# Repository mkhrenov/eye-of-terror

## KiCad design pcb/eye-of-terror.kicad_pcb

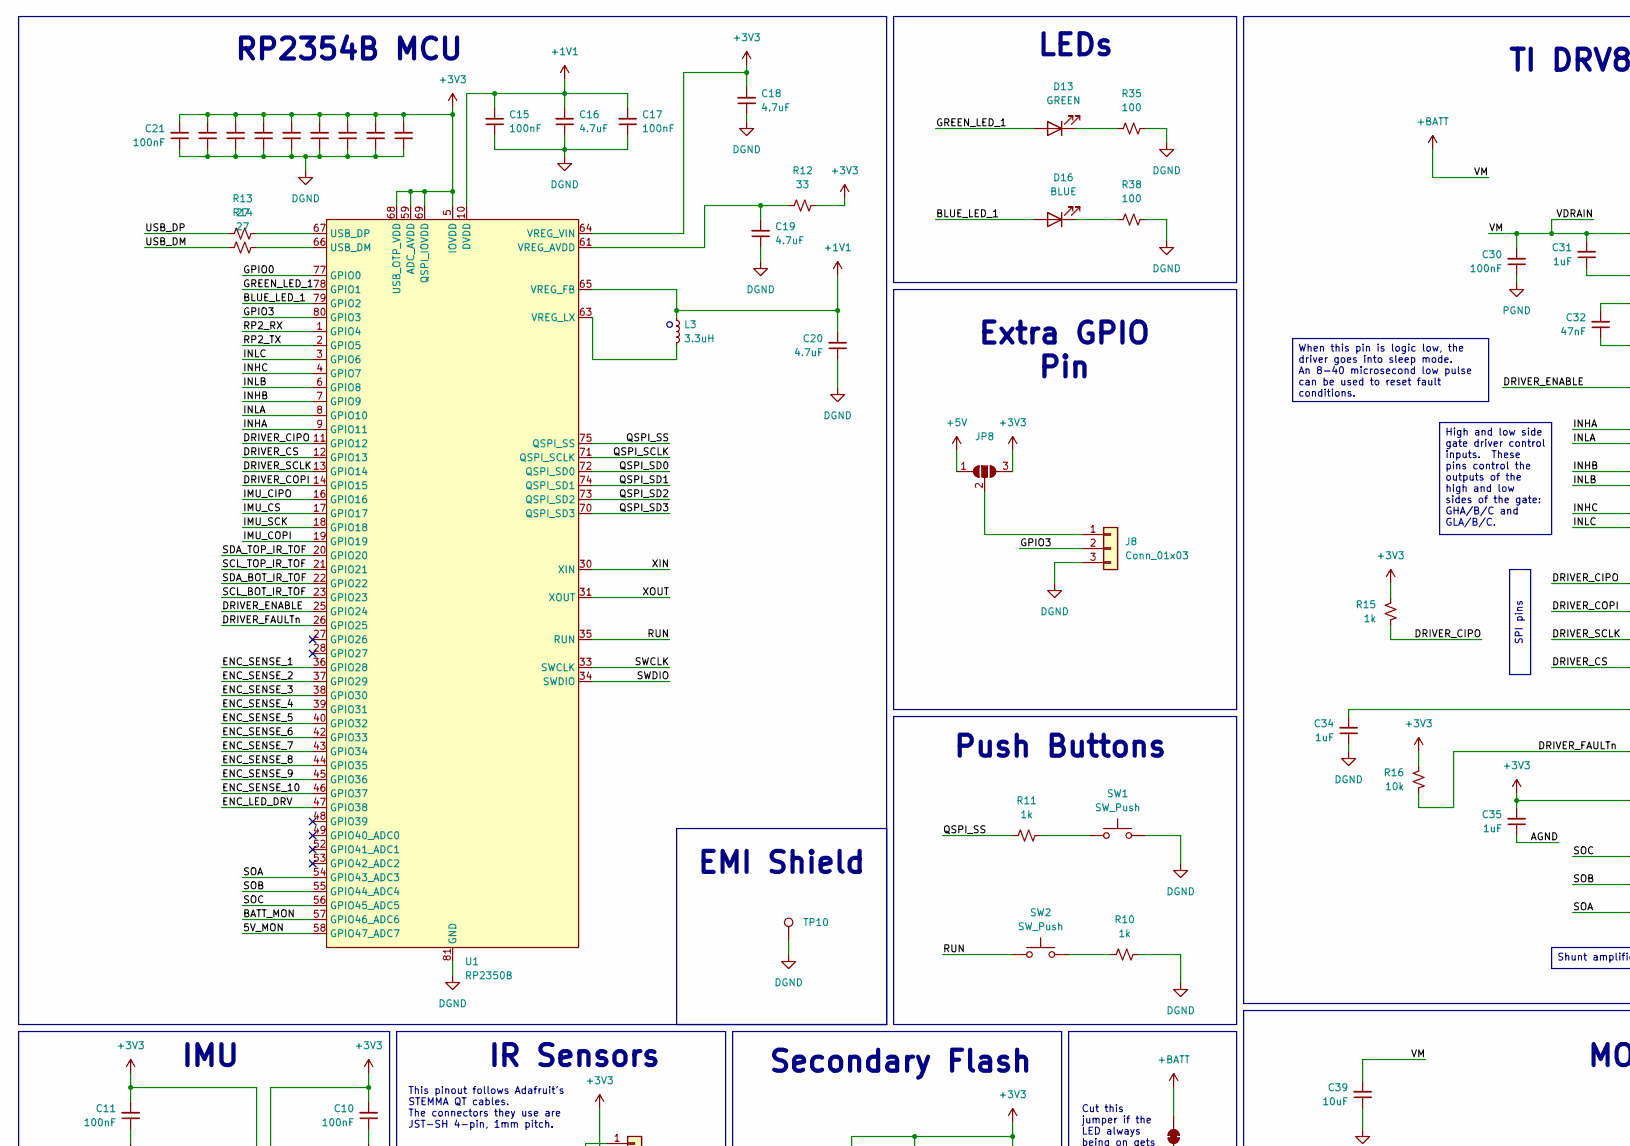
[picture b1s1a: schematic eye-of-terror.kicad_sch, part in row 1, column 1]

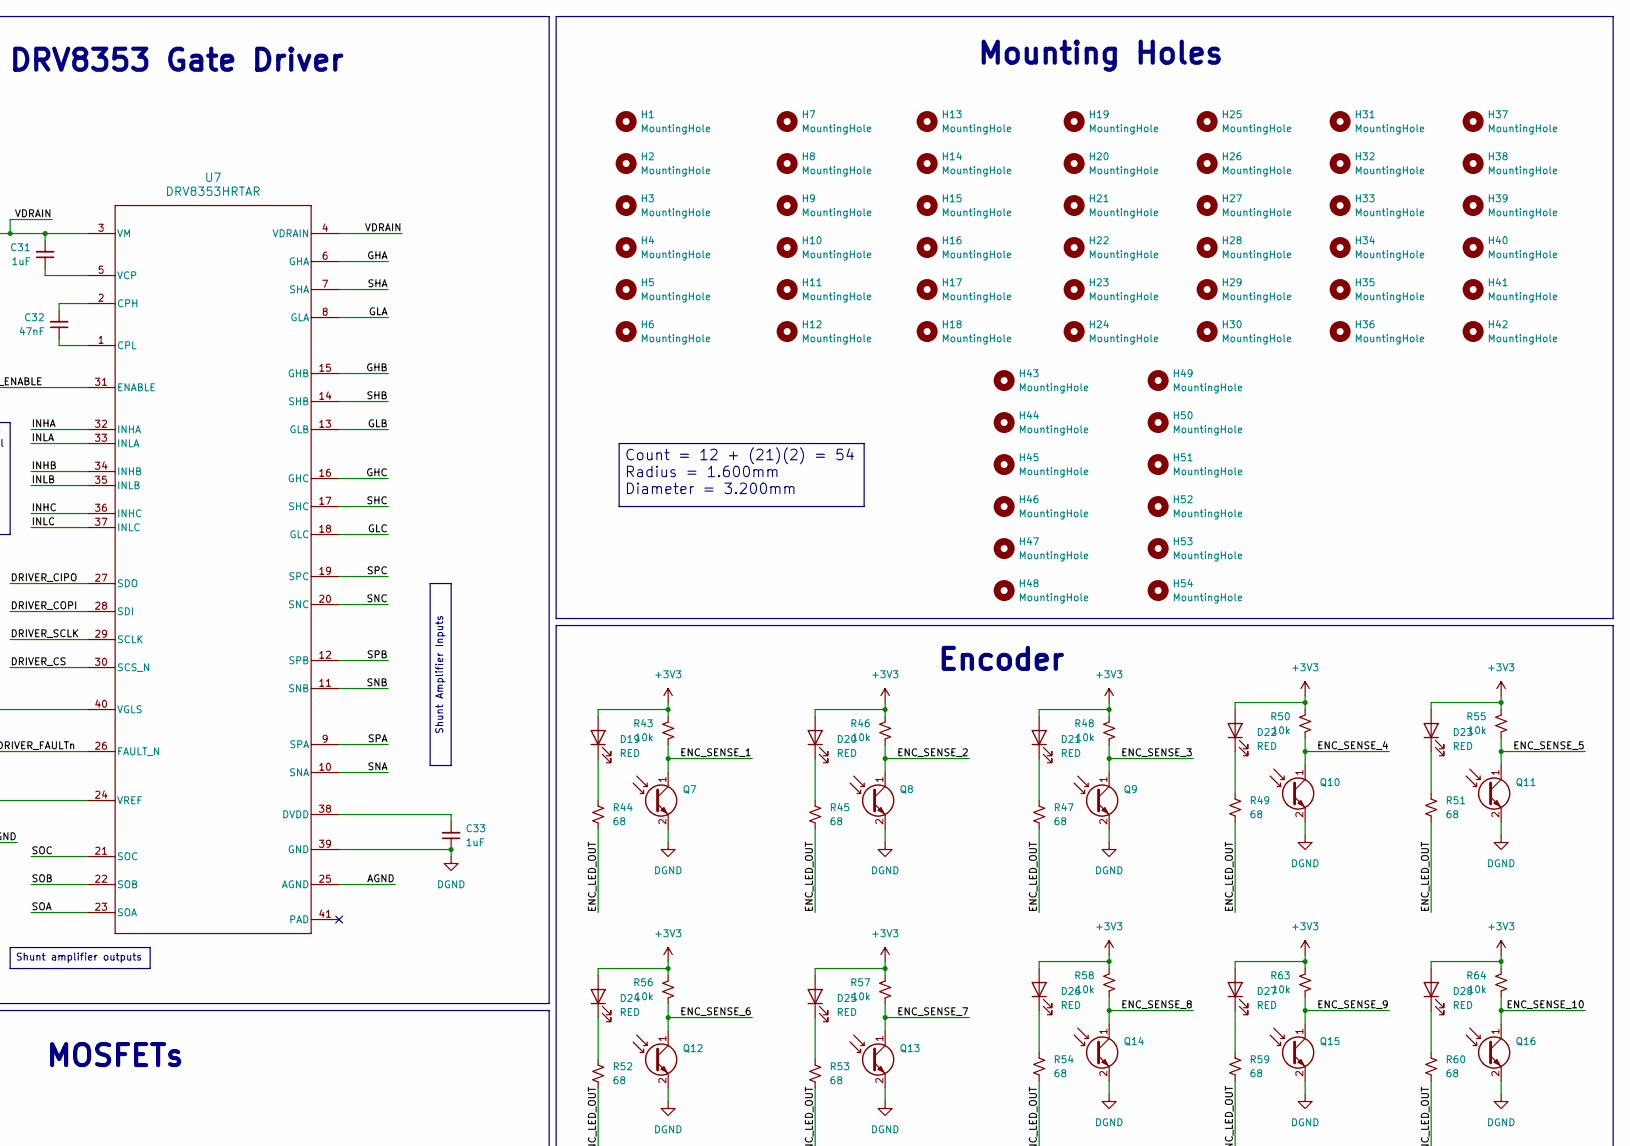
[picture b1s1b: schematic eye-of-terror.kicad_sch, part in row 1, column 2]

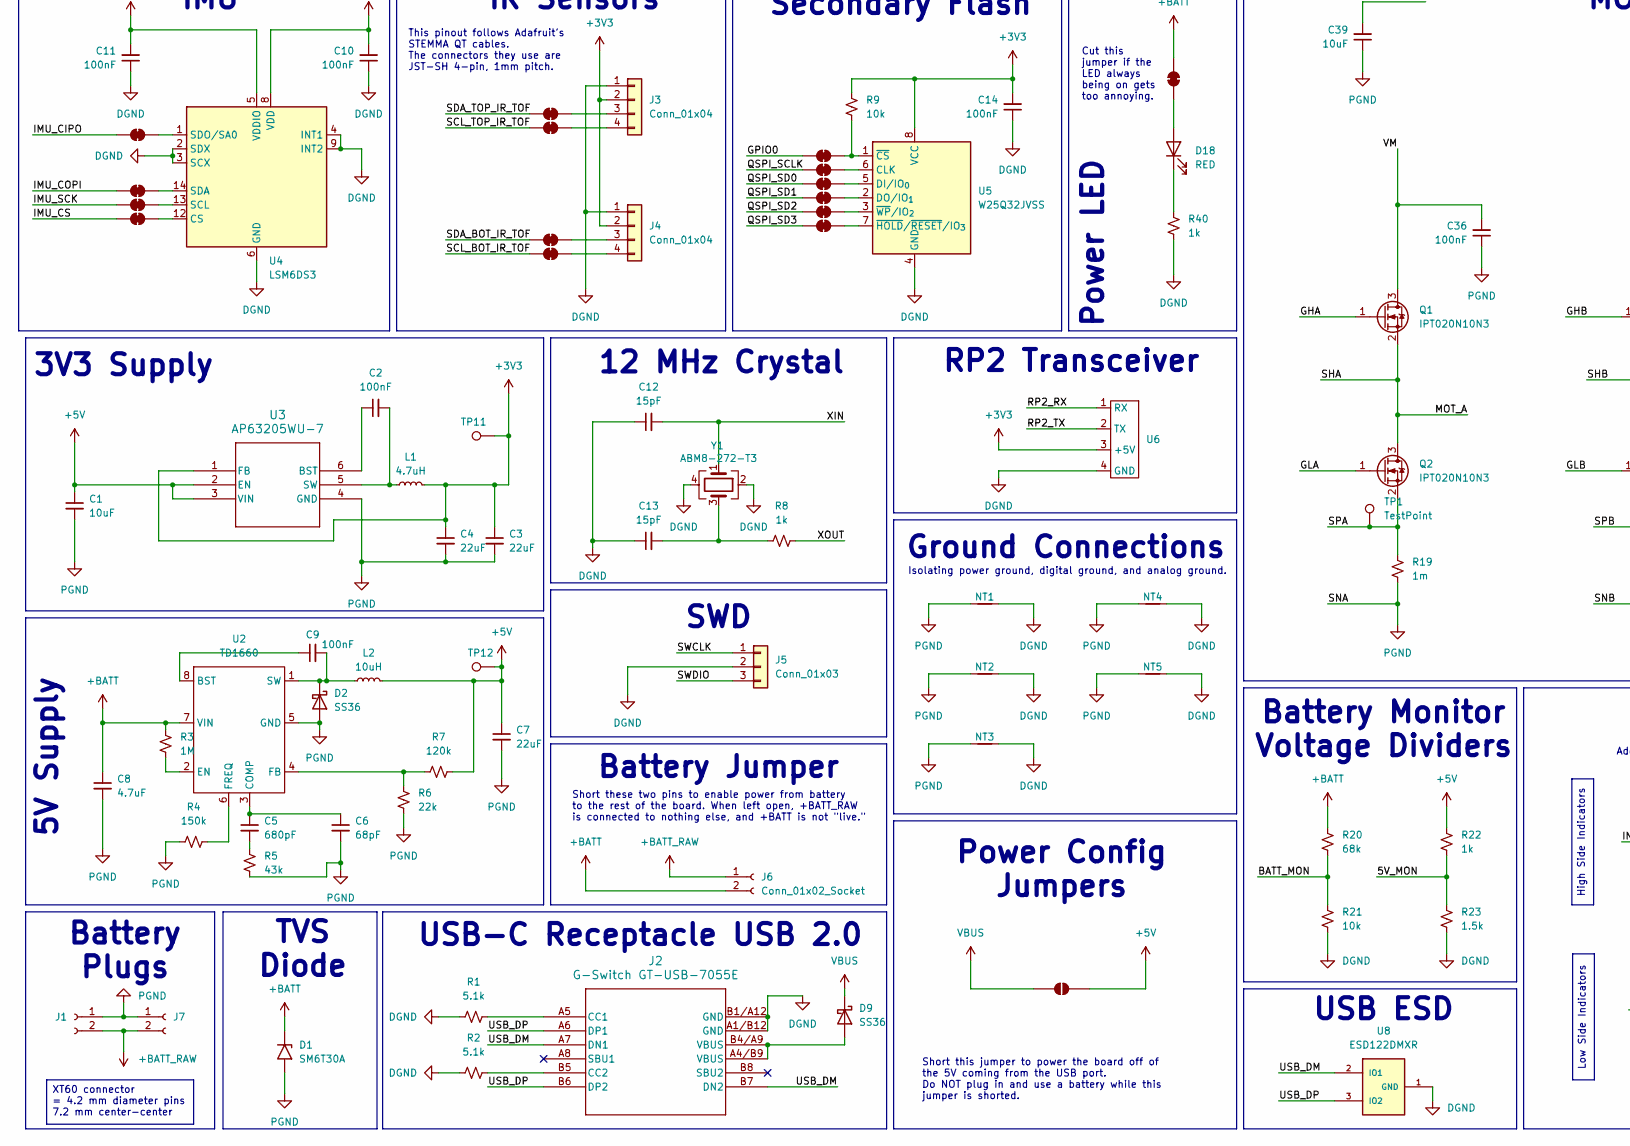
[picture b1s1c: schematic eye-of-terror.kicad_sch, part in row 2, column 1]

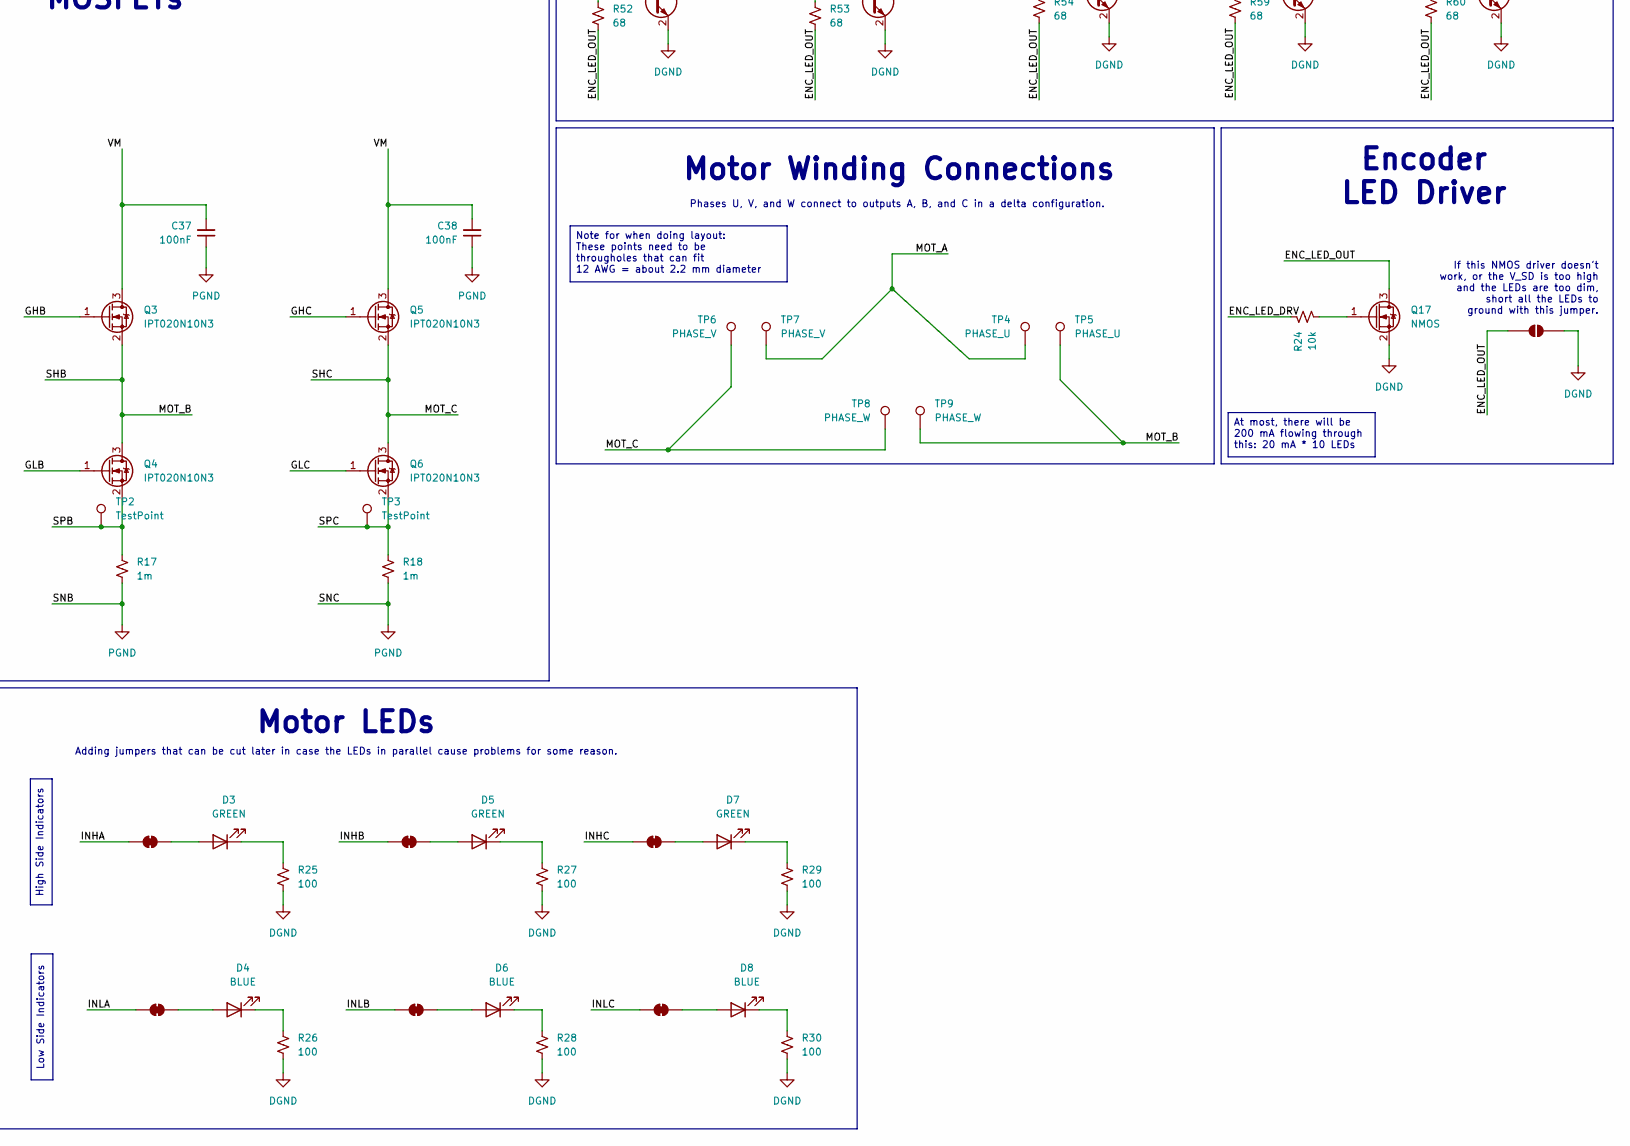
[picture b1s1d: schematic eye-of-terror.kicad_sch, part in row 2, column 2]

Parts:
C1, C39: 10uF; CP_Elec_5x5.4; LCSC Number C72487
C2, C9, C30, C36, C37, C38: 100nF; C_0603_1608Metric_Pad1.08x0.95mm_HandSolder; LCSC Number C14663
C3, C4, C7: 22uF; C_0603_1608Metric_Pad1.08x0.95mm_HandSolder; LCSC Number C86295
C5: 680pF; C_0402_1005Metric_Pad0.74x0.62mm_HandSolder; LCSC Number C307451
C6: 68pF; C_0603_1608Metric_Pad1.08x0.95mm_HandSolder; LCSC Number C62782
C8, C16, C18, C19, C20: 4.7uF; C_0402_1005Metric_Pad0.74x0.62mm_HandSolder; LCSC Number C23733
C10, C11, C14, C15, C17, C21, C22, C23, C24, C25, C26, C27, C28, C29: 100nF; C_0402_1005Metric_Pad0.74x0.62mm_HandSolder; LCSC Number C60474
C12, C13: 15pF; C_0402_1005Metric_Pad0.74x0.62mm_HandSolder; LCSC Number C86285
C31, C33, C34, C35: 1uF; C_0603_1608Metric_Pad1.08x0.95mm_HandSolder; LCSC Number C15849
C32: 47nF; C_0402_1005Metric_Pad0.74x0.62mm_HandSolder; LCSC Number C368599
D1: SM6T30A; D_SMB; LCSC Number C110904
D2, D9: SS36; D_SMB; LCSC Number C35490
D3, D5, D7, D13: GREEN; D_1206_3216Metric_Pad1.42x1.75mm_HandSolder; LCSC Number C965825
D4, D6, D8, D16: BLUE; D_1206_3216Metric_Pad1.42x1.75mm_HandSolder; LCSC Number C965827
D18, D19, D20, D21, D22, D23, D24, D25, D26, D27, D28: RED; D_1206_3216Metric_Pad1.42x1.75mm_HandSolder; LCSC Number C2984265
H1, H2, H3, H4, H5, H6, H7, H8, H9, H10, H11, H12, H13, H14, H15, H16, H17, H18, H19, H20, H21, H22, H23, H24, H25, H26, H27, H28, H29, H30, H31, H32, H33, H34, H35, H36, H37, H38, H39, H40, H41, H42, H43, H44, H45, H46, H47, H48, H49, H50, H51, H52, H53, H54: MountingHole; MountingHole_3.2mm_M3
J1, J6, J7: Conn_01x02_Socket; AMASS_XT60-M_1x02_P7.20mm_Vertical
J2: G-Switch GT-USB-7055E; CONN_GT-USB-7055A_GSW; LCSC Number C7450622
J3, J4: Conn_01x04; PinHeader_1x04_P1.00mm_Vertical
J5, J8: Conn_01x03; PinHeader_1x03_P2.54mm_Vertical
JP1, JP2, JP3, JP4, JP5, JP6, JP7, JP9, JP10, JP11, JP12, JP13, JP14, JP15, JP16, JP19, JP20, JP21, JP22, JP23, JP24: SolderJumper_2_Bridged; SolderJumper-2_P1.3mm_Bridged_RoundedPad1.0x1.5mm
JP8: SolderJumper_3_Open; SolderJumper-3_P1.3mm_Open_RoundedPad1.0x1.5mm_NumberLabels
JP17, JP18: SolderJumper_2_Bridged; SolderJumper-2_P1.3mm_Open_RoundedPad1.0x1.5mm
L1: 4.7uH; IND_LQH5BPZ4R7NT0L; LCSC Number C703747
L2: 10uH; L_Sunlord_MWSA0402S; LCSC Number C2921170
L3: 3.3uH; ABRACON-AOTA-B201610S3R3-101-T; LCSC Number C42411119
NT1, NT2, NT3, NT4, NT5: NetTie_2; NetTie-2_SMD_Pad2.0mm
Q1, Q2, Q3, Q4, Q5, Q6: IPT020N10N3; Infineon_PG-HSOF-8-1_ThermalVias; LCSC Number C537070
Q7, Q8, Q9, Q10, Q11, Q12, Q13, Q14, Q15, Q16: ALS-PT19-315C/L177/TR8; LED_0603_1608Metric_Pad1.05x0.95mm_HandSolder; LCSC Number C146233
Q17: NMOS; TSOT-23_HandSoldering
R1, R2: 5.1k; R_0402_1005Metric_Pad0.72x0.64mm_HandSolder; LCSC Number C114759
R3: 1M; R_0603_1608Metric_Pad0.98x0.95mm_HandSolder; LCSC Number C105578
R4: 150k; R_0402_1005Metric_Pad0.72x0.64mm_HandSolder; LCSC Number C93947
R5: 43k; R_0603_1608Metric_Pad0.98x0.95mm_HandSolder; LCSC Number C2907038
R6: 22k; R_0603_1608Metric_Pad0.98x0.95mm_HandSolder; LCSC Number C114065
R7: 120k; R_0603_1608Metric_Pad0.98x0.95mm_HandSolder; LCSC Number C114607
R8, R10, R11, R15, R22: 1k; R_0402_1005Metric_Pad0.72x0.64mm_HandSolder; LCSC Number C106235
R9, R16, R21, R24, R43, R46, R48, R50, R55, R56, R57, R58, R63, R64: 10k; R_0402_1005Metric_Pad0.72x0.64mm_HandSolder; LCSC Number C60490
R12: 33; R_0402_1005Metric_Pad0.72x0.64mm_HandSolder; LCSC Number C138002
R13, R14: 27; R_0402_1005Metric_Pad0.72x0.64mm_HandSolder; LCSC Number C25100
R17, R18, R19: 1m; R_1206_3216Metric_Pad1.30x1.75mm_HandSolder; LCSC Number C7467246
R20: 68k; R_0603_1608Metric_Pad0.98x0.95mm_HandSolder; LCSC Number C23231
R23: 1.5k; R_1210_3225Metric_Pad1.30x2.65mm_HandSolder; LCSC Number C3000602
R25, R26, R27, R28, R29, R30, R35, R38: 100; R_0603_1608Metric_Pad0.98x0.95mm_HandSolder; LCSC Number C105588
R40: 1k; R_0603_1608Metric_Pad0.98x0.95mm_HandSolder; LCSC Number C22548
R44, R45, R47, R49, R51, R52, R53, R54, R59, R60: 68; R_0402_1005Metric_Pad0.72x0.64mm_HandSolder; LCSC Number C163455
SW1, SW2: SW_Push; SW_Push_SPST_NO_Alps_SKRK; LCSC Number C720477
TP1, TP2, TP3: TestPoint; TestPoint_Pad_D2.5mm
TP4, TP5: PHASE_U; THTPad_D5.0mm_Drill2.5mm
TP6, TP7: PHASE_V; THTPad_D5.0mm_Drill2.5mm
TP8, TP9: PHASE_W; THTPad_D5.0mm_Drill2.5mm
TP10: TestPoint; shielding
TP11, TP12: TestPoint; TestPoint_Pad_D1.0mm
U1: RP2350B; QFN-80-1EP_10x10mm_P0.4mm_EP3.4x3.4mm_ThermalVias; LCSC Number C39843328
U2: TD1660; TD1660-SOIC-8; LCSC Number C2832211
U3: AP63205WU-7; SOIC_05WU-7_DIO; LCSC Number C780769
U4: LSM6DS3; LGA-14_3x2.5mm_P0.5mm_LayoutBorder3x4y; LCSC Number C95230
U5: W25Q32JVSS; SOIC-8_5.3x5.3mm_P1.27mm; LCSC Number C97521
U6: RP2
U7: DRV8353HRTAR; RTA0040B; LCSC Number C1518717
U8: ESD122DMXR; IC_ESD122DMXR; PARTREV A
Y1: ABM8-272-T3; Crystal_SMD_3225-4Pin_3.2x2.5mm; LCSC Number C20625731

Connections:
+1V1: C15.2, C16.2, C17.2, C20.2, L3.1, U1.10 (DVDD), U1.32 (DVDD), U1.51 (DVDD), U1.65 (VREG_FB)
+3V3: C3.1, C4.1, C10.2, C11.2, C14.2, C18.2, C21.2, C22.2, C23.2, C24.2, C25.2, C26.2, C27.2, C28.2, C29.2, C35.2, D19.2 (A), D20.2 (A), D21.2 (A), D22.2 (A), D23.2 (A), D24.2 (A), D25.2 (A), D26.2 (A), D27.2 (A), D28.2 (A), J3.2, J4.2, JP8.3 (B), L1.2, R9.1, R12.2, R15.1, R16.1, R43.1, R46.1, R48.1, R50.1, R55.1, R56.1, R57.1, R58.1, R63.1, R64.1, TP11.1 (1_1), U1.5 (IOVDD), U1.15 (IOVDD), U1.24 (IOVDD), U1.29 (IOVDD), U1.41 (IOVDD), U1.50 (IOVDD), U1.59 (ADC_AVDD), U1.60 (IOVDD), U1.64 (VREG_VIN), U1.68 (USB_OTP_VDD), U1.69 (QSPI_IOVDD), U1.76 (IOVDD), U3.1 (FB), U4.5 (VDDIO), U4.8 (VDD), U5.8 (VCC), U6.3 (+5V), U7.24 (VREF)
+5V: C1.1, C7.1, JP8.1 (A), JP17.2 (B), L2.2, R7.2, R22.1, TP12.1 (1_1), U3.2 (EN), U3.3 (VIN)
+BATT: C8.1, C30.2, C31.2, C36.2, C37.2, C38.2, C39.2, D1.1 (A1), J6.2, JP16.2 (B), Q1.3 (D), Q3.3 (D), Q5.3 (D), R3.1, R20.1, U2.7 (VIN), U7.3 (VM), U7.4 (VDRAIN)
+BATT_RAW: J1.2, J6.1, J7.2
/5V_MON: R22.2, R23.1, U1.58 (GPIO47_ADC7)
/AGND: C35.1, U7.25 (AGND)
/BATT_MON: R20.2, R21.1, U1.57 (GPIO46_ADC6)
/BLUE_LED_1: D16.2 (A), U1.79 (GPIO2)
/DRIVER_CIPO: R15.2, U1.11 (GPIO12), U7.27 (SDO)
/DRIVER_COPI: U1.14 (GPIO15), U7.28 (SDI)
/DRIVER_CS: U1.12 (GPIO13), U7.30 (SCS_N)
/DRIVER_ENABLE: U1.25 (GPIO24), U7.31 (ENABLE)
/DRIVER_FAULTn: R16.2, U1.26 (GPIO25), U7.26 (FAULT_N)
/DRIVER_SCLK: U1.13 (GPIO14), U7.29 (SCLK)
/ENC_LED_DRV: R24.1, U1.47 (GPIO38)
/ENC_LED_OUT: JP18.1 (A), Q17.3 (D), R44.2, R45.2, R47.2, R49.2, R51.2, R52.2, R53.2, R54.2, R59.2, R60.2
/ENC_SENSE_1: Q7.1 (C), R43.2, U1.36 (GPIO28)
/ENC_SENSE_2: Q8.1 (C), R46.2, U1.37 (GPIO29)
/ENC_SENSE_3: Q9.1 (C), R48.2, U1.38 (GPIO30)
/ENC_SENSE_4: Q10.1 (C), R50.2, U1.39 (GPIO31)
/ENC_SENSE_5: Q11.1 (C), R55.2, U1.40 (GPIO32)
/ENC_SENSE_6: Q12.1 (C), R56.2, U1.42 (GPIO33)
/ENC_SENSE_7: Q13.1 (C), R57.2, U1.43 (GPIO34)
/ENC_SENSE_8: Q14.1 (C), R58.2, U1.44 (GPIO35)
/ENC_SENSE_9: Q15.1 (C), R63.2, U1.45 (GPIO36)
/ENC_SENSE_10: Q16.1 (C), R64.2, U1.46 (GPIO37)
/GHA: Q1.1 (G), U7.6 (GHA)
/GHB: Q3.1 (G), U7.15 (GHB)
/GHC: Q5.1 (G), U7.16 (GHC)
/GLA: Q2.1 (G), U7.8 (GLA)
/GLB: Q4.1 (G), U7.13 (GLB)
/GLC: Q6.1 (G), U7.18 (GLC)
/GPIO0: JP19.1 (A), U1.77 (GPIO0)
/GPIO3: J8.2, U1.80 (GPIO3)
/GREEN_LED_1: D13.2 (A), U1.78 (GPIO1)
/IMU_CIPO: JP4.1 (A), U1.16 (GPIO16)
/IMU_COPI: JP5.1 (A), U1.19 (GPIO19)
/IMU_CS: JP7.1 (A), U1.17 (GPIO17)
/IMU_SCK: JP6.1 (A), U1.18 (GPIO18)
/INHA: JP10.1 (A), U1.9 (GPIO11), U7.32 (INHA)
/INHB: JP12.1 (A), U1.7 (GPIO9), U7.34 (INHB)
/INHC: JP14.1 (A), U1.4 (GPIO7), U7.36 (INHC)
/INLA: JP11.1 (A), U1.8 (GPIO10), U7.33 (INLA)
/INLB: JP13.1 (A), U1.6 (GPIO8), U7.35 (INLB)
/INLC: JP15.1 (A), U1.3 (GPIO6), U7.37 (INLC)
/MOT_A: Q1.2 (S), Q2.3 (D), TP4.1 (1_1), TP7.1 (1_1), U7.7 (SHA)
/MOT_B: Q3.2 (S), Q4.3 (D), TP5.1 (1_1), TP9.1 (1_1), U7.14 (SHB)
/MOT_C: Q5.2 (S), Q6.3 (D), TP6.1 (1_1), TP8.1 (1_1), U7.17 (SHC)
/QSPI_SCLK: JP20.1 (A), U1.71 (QSPI_SCLK)
/QSPI_SD0: JP21.1 (A), U1.72 (QSPI_SD0)
/QSPI_SD1: JP22.1 (A), U1.74 (QSPI_SD1)
/QSPI_SD2: JP23.1 (A), U1.73 (QSPI_SD2)
/QSPI_SD3: JP24.1 (A), U1.70 (QSPI_SD3)
/QSPI_SS: R11.1, U1.75 (QSPI_SS)
/RP2_RX: U1.1 (GPIO4), U6.1 (RX)
/RP2_TX: U1.2 (GPIO5), U6.2 (TX)
/RUN: SW2.1, U1.35 (RUN)
/SCL_BOT_IR_TOF: JP3.1 (A), U1.23 (GPIO23)
/SCL_TOP_IR_TOF: JP9.1 (A), U1.21 (GPIO21)
/SDA_BOT_IR_TOF: JP2.1 (A), U1.22 (GPIO22)
/SDA_TOP_IR_TOF: JP1.1 (A), U1.20 (GPIO20)
/SOA: U1.54 (GPIO43_ADC3), U7.23 (SOA)
/SOB: U1.55 (GPIO44_ADC4), U7.22 (SOB)
/SOC: U1.56 (GPIO45_ADC5), U7.21 (SOC)
/SPA: Q2.2 (S), R19.1, TP1.1 (1_1), U7.9 (SPA)
/SPB: Q4.2 (S), R17.1, TP2.1 (1_1), U7.12 (SPB)
/SPC: Q6.2 (S), R18.1, TP3.1 (1_1), U7.19 (SPC)
/SWCLK: J5.1, U1.33 (SWCLK)
/SWDIO: J5.3, U1.34 (SWDIO)
/USB_DM: J2.A7 (DN1), J2.B7 (DN2), R14.1, U8.2 (IO1)
/USB_DP: J2.A6 (DP1), J2.B6 (DP2), R13.1, U8.3 (IO2)
/XIN: C12.2, U1.30 (XIN), Y1.1
/XOUT: R8.2, U1.31 (XOUT)
DGND: C10.1, C11.1, C12.1, C13.1, C14.1, C15.1, C16.1, C17.1, C18.1, C19.1, C20.1, C21.1, C22.1, C23.1, C24.1, C25.1, C26.1, C27.1, C28.1, C29.1, C33.1, C34.1, J2.A1/B12 (GND), J2.B1/A12 (GND), J3.1, J4.1, J5.2, J8.3, JP18.2 (B), NT1.2, NT2.2, NT3.2, NT4.2, NT5.2, Q7.2 (E), Q8.2 (E), Q9.2 (E), Q10.2 (E), Q11.2 (E), Q12.2 (E), Q13.2 (E), Q14.2 (E), Q15.2 (E), Q16.2 (E), Q17.2 (S), R1.1, R2.1, R10.2, R21.2, R23.2, R25.2, R26.2, R27.2, R28.2, R29.2, R30.2, R35.2, R38.2, R40.1, SW1.2, TP10.1, U1.62 (VREG_PGND), U1.81 (GND), U4.2 (SDX), U4.3 (SCX), U4.4 (INT1), U4.6 (GND), U4.7 (GND), U4.9 (INT2), U5.4 (GND), U6.4 (GND), U7.39 (GND), U8.1 (GND), Y1.2, Y1.4
unnamed: C5.2, R5.1
unnamed: C13.2, R8.1, Y1.3
unnamed: C9.2, D2.1 (K), L2.1, U2.1 (SW)
unnamed: D3.2 (A), JP10.2 (B)
unnamed: D3.1 (K), R25.1
unnamed: D4.2 (A), JP11.2 (B)
unnamed: D4.1 (K), R26.1
unnamed: D5.2 (A), JP12.2 (B)
unnamed: D5.1 (K), R27.1
unnamed: D6.2 (A), JP13.2 (B)
unnamed: D6.1 (K), R28.1
unnamed: D7.2 (A), JP14.2 (B)
unnamed: D7.1 (K), R29.1
unnamed: D8.2 (A), JP15.2 (B)
unnamed: D8.1 (K), R30.1
unnamed: D9.2 (A), J2.A4/B9 (VBUS), J2.B4/A9 (VBUS)
unnamed: D13.1 (K), R35.1
unnamed: D16.1 (K), R38.1
unnamed: D18.2 (A), JP16.1 (A)
unnamed: D18.1 (K), R40.2
unnamed: D19.1 (K), R44.1
unnamed: D20.1 (K), R45.1
unnamed: D21.1 (K), R47.1
unnamed: D22.1 (K), R49.1
unnamed: D23.1 (K), R51.1
unnamed: D24.1 (K), R52.1
unnamed: D25.1 (K), R53.1
unnamed: D26.1 (K), R54.1
unnamed: D27.1 (K), R59.1
unnamed: D28.1 (K), R60.1
unnamed: J2.A5 (CC1), R1.2
unnamed: J2.B5 (CC2), R2.2
unnamed: J3.3, JP1.2 (B)
unnamed: J3.4, JP9.2 (B)
unnamed: J4.3, JP2.2 (B)
unnamed: J4.4, JP3.2 (B)
unnamed: J8.1, JP8.2 (C)
unnamed: JP4.2 (B), U4.1 (SDO/SA0)
unnamed: JP5.2 (B), U4.14 (SDA)
unnamed: JP6.2 (B), U4.13 (SCL)
unnamed: JP7.2 (B), U4.12 (CS)
unnamed: JP19.2 (B), R9.2, U5.1 (~CS)
unnamed: JP20.2 (B), U5.6 (CLK)
unnamed: JP21.2 (B), U5.5 (DI/IO_{0})
unnamed: JP22.2 (B), U5.2 (DO/IO_{1})
unnamed: JP23.2 (B), U5.3 (~WP/IO_{2})
unnamed: JP24.2 (B), U5.7 (~HOLD/~RESET/IO_{3})
unnamed: Q17.1 (G), R24.2
unnamed: R10.1, SW2.2
unnamed: R11.2, SW1.1
unnamed: R14.2, U1.66 (USB_DM)
unnamed: R13.2, U1.67 (USB_DP)
unnamed: C19.2, R12.1, U1.61 (VREG_AVDD)
unnamed: L3.2, U1.63 (VREG_LX)
unnamed: C9.1, U2.8 (BST)
unnamed: C5.1, C6.1, U2.3 (COMP)
unnamed: R3.2, U2.2 (EN)
unnamed: R6.1, R7.1, U2.4 (FB)
unnamed: R4.1, U2.6 (FREQ)
unnamed: C2.1, U3.6 (BST)
unnamed: C2.2, L1.1, U3.5 (SW)
unnamed: C32.2, U7.2 (CPH)
unnamed: C32.1, U7.1 (CPL)
unnamed: C33.2, U7.38 (DVDD)
unnamed: C31.1, U7.5 (VCP)
unnamed: C34.2, U7.40 (VGLS)
PGND: C1.2, C3.2, C4.2, C6.2, C7.2, C8.2, C30.1, C36.1, C37.1, C38.1, C39.1, D1.2 (A2), D2.2 (A), J1.1, J7.1, NT1.1, NT2.1, NT3.1, NT4.1, NT5.1, R4.2, R5.2, R6.2, R17.2, R18.2, R19.2, U2.5 (GND), U3.4 (GND), U7.10 (SNA), U7.11 (SNB), U7.20 (SNC)
VBUS: D9.1 (K), JP17.1 (A)

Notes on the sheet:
TI DRV8353 Gate Driver
Push Buttons
Secondary Flash
Encoder LED Driver
Motor Winding Connections
12 MHz Crystal
IMU
TVS Diode
Ground Connections
Phases U, V, and W connect to outputs A, B, and C in a delta configuration.
RP2354B MCU
3V3 Supply
Motor LEDs
RP2 Transceiver
EMI Shield
IR Sensors
Battery Jumper
Encoder
LEDs
If this NMOS driver doesn't work, or the V_SD is too high and the LEDs are too dim, short all the LEDs to ground with this jumper.
USB-C Receptacle USB 2.0
5V Supply
Isolating power ground, digital ground, and analog ground.
Power Config Jumpers
Battery Monitor Voltage Dividers
Power LED
Short these two pins to enable power from battery to the rest of the board. When left open, +BATT_RAW is connected to nothing else, and +BATT is not "live."
Short this jumper to power the board off of the 5V coming from the USB port. Do NOT plug in and use a battery while this jumper is shorted.
This pinout follows Adafruit's STEMMA QT cables. The connectors they use are JST-SH 4-pin, 1mm pitch.
SWD
Adding jumpers that can be cut later in case the LEDs in parallel cause problems for some reason.
Mounting Holes
Cut this jumper if the LED always being on gets too annoying.
MOSFETs
USB ESD
Extra GPIO Pin
Battery Plugs
High Side Indicators
XT60 connector = 4.2 mm diameter pins 7.2 mm center-center
At most, there will be 200 mA flowing through this: 20 mA * 10 LEDs

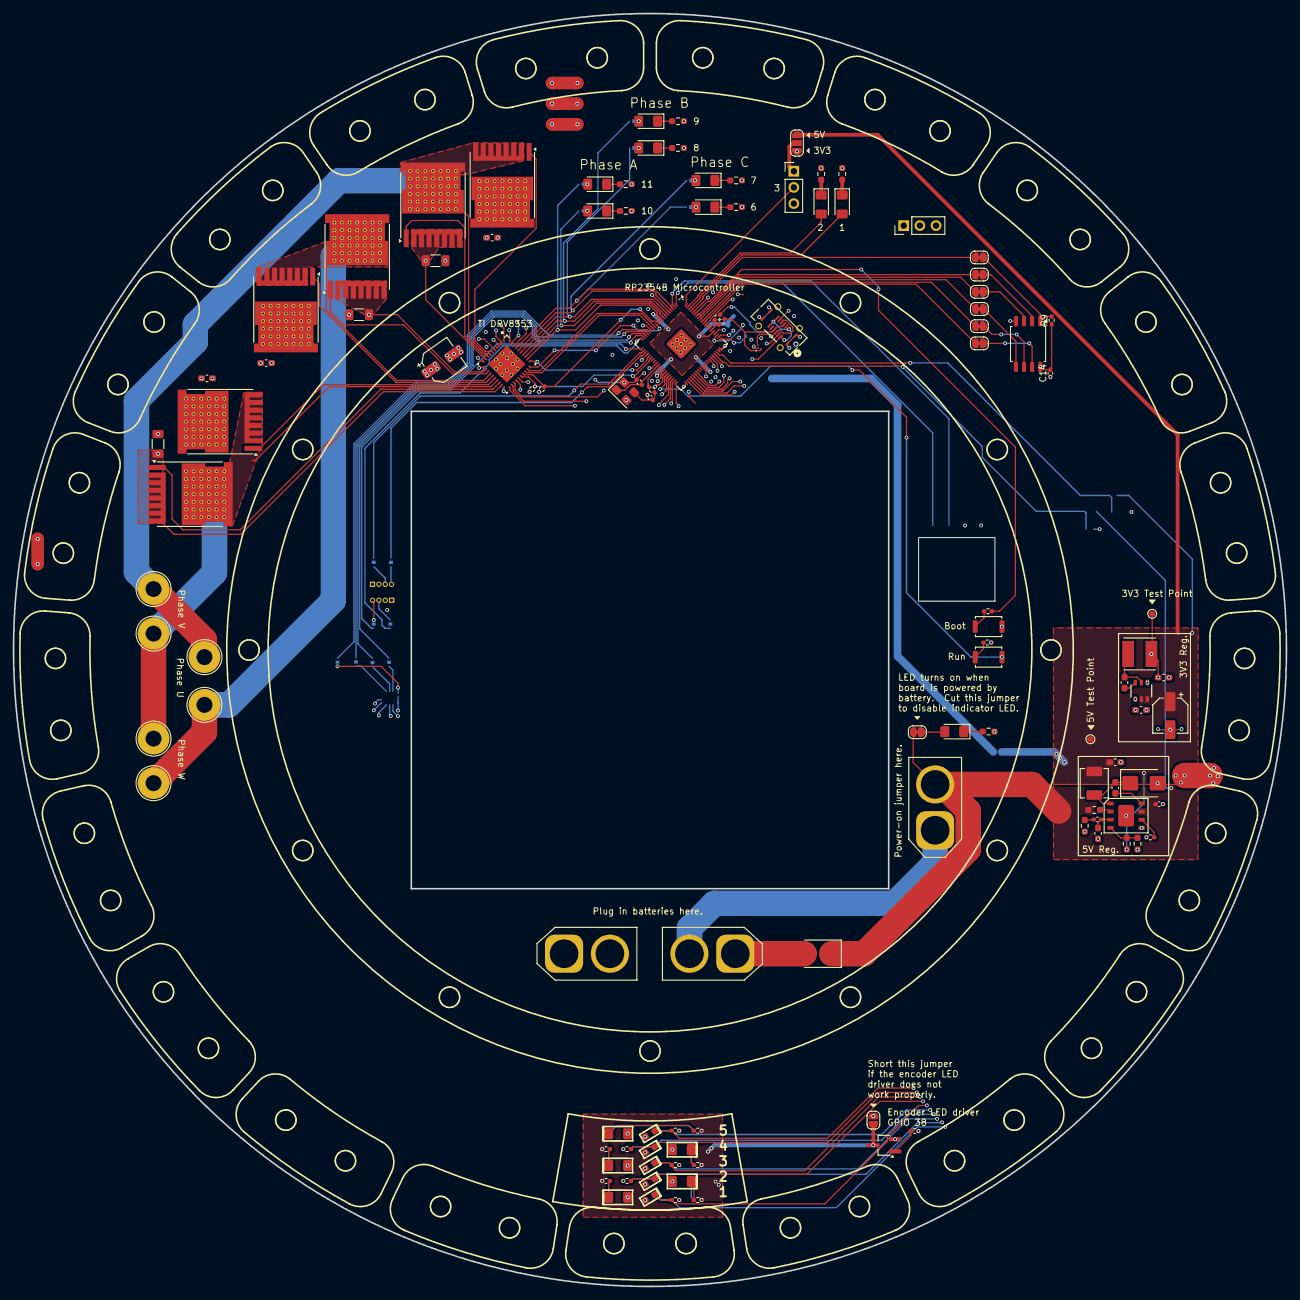
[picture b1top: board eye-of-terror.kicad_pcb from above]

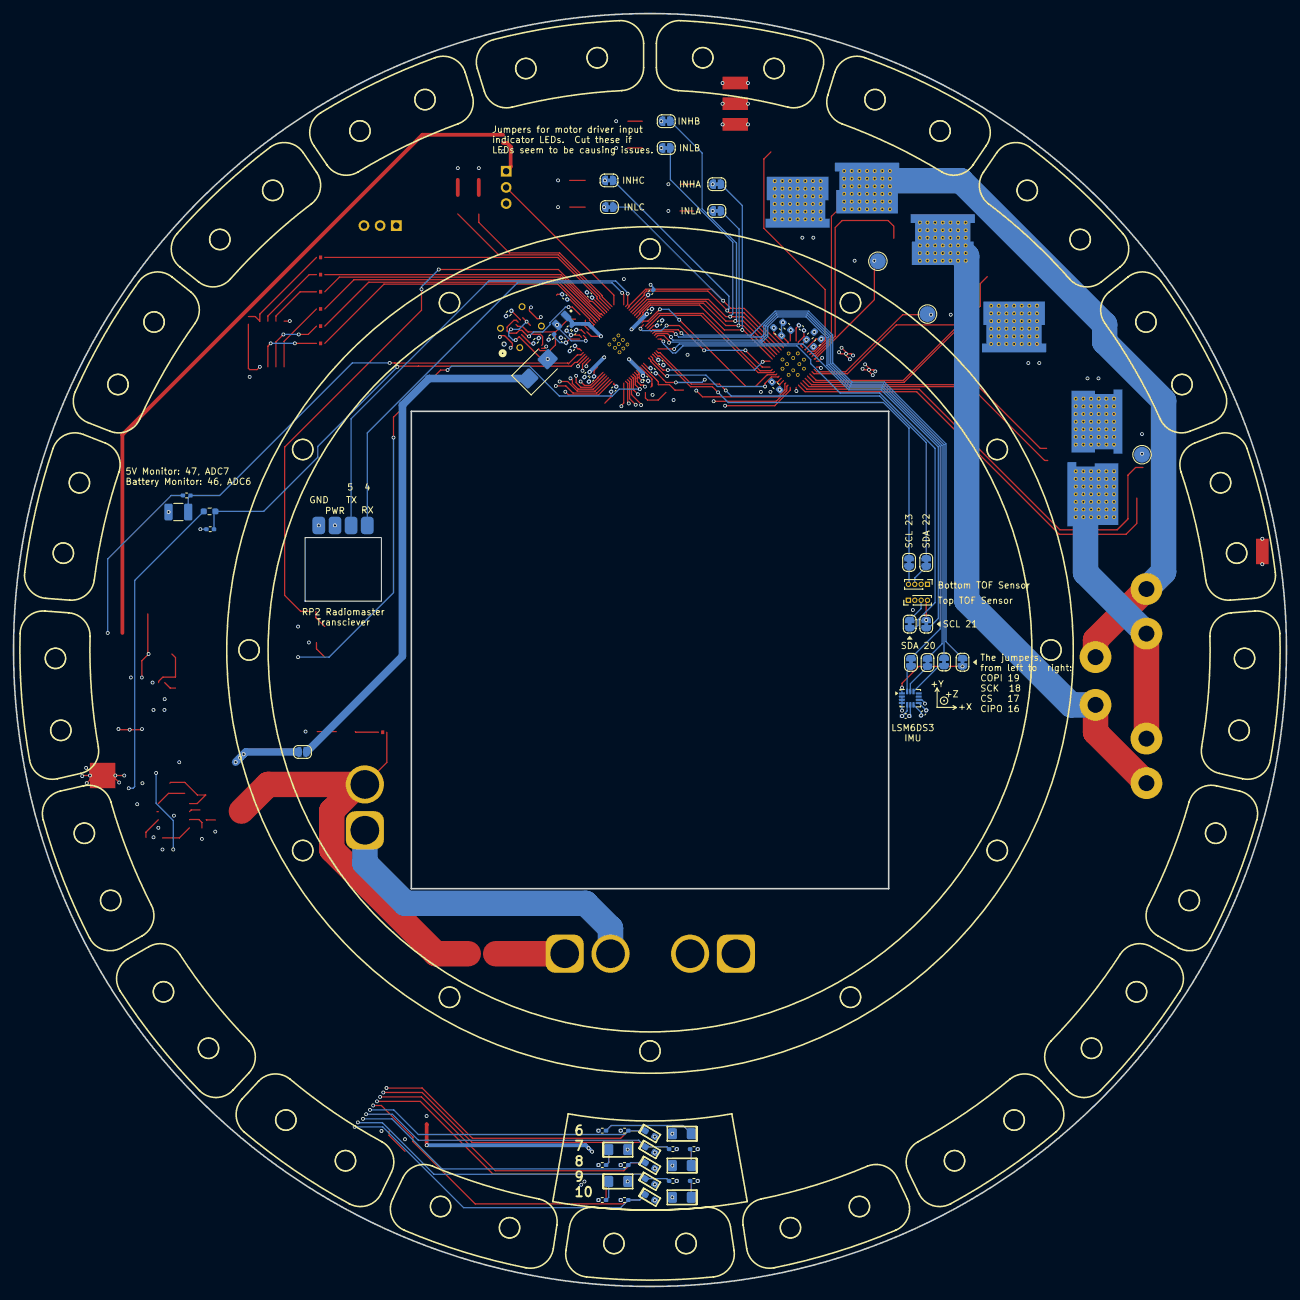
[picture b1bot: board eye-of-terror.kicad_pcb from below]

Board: 4 copper layers, 200.0 x 200.0 mm, 247 parts (74 on the bottom side), 143 nets.

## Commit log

2025-09-17 ironless-halbach motor calculator
2025-09-17 Adjusted coil area calculation
2025-09-20 Stator, but heavy. will delete
2025-09-27 New rotor
2025-10-14 Robot model skeleton
2025-10-15 Motor fields
2025-10-29 Airfoil force functions
2025-10-29 Axial flux motor characteristic functions
2025-11-15 Nuked old CAD
2025-11-15 New rotor and stator arch (still need magnets, coils, fasteners, sensors)
2025-11-15 Landing struts/fins
2025-11-16 Added coils and magnets to CAD, adjusted dimensions
2025-11-16 asm tweak
2025-12-14 Near final CAD with fasteners and TPU fins
2025-12-14 Manufacturing files
2025-12-21 added folder for pcb, started schematic
2025-12-22 More manufacturing stuff
2025-12-22 Updated geometry to reduce AOA with twist
2025-12-25 Updated angle of attack to account for downward air velocity
2025-12-28 Standard NACA 0006
2025-12-31 all components added to schematic
    still need to add GPIO pin labels.
    next step after that is to verify footprints for everything.
2026-01-02 added gpio labels and indicator LEDs
2026-01-05 fixed bugs in schematic, added most footprints
2026-01-06 all footprints checked and added
2026-01-07 PCB DXF
2026-01-07 added extra breakout GPIO pins, imported PCB DXF
2026-01-08 WIP layout, most components placed
2026-01-09 WIP layout
2026-01-10 re-routed mosfets for better layout
2026-01-11 updated smaller footprints for some components
    added lock files to gitignore
2026-01-19 updated schematic to include encoder and RP2040
    passes ERC (excluding the errors that can be safetly ignored)
2026-01-24 Revert "Standard NACA 0006"
    This reverts commit 69dd74f3e7babb22d99644cc8a0a3e954418e0ed.
2026-01-24 166 mm Ti64 symmetric blade and counterweight
2026-02-01 deleted the RP2040
    because direct control of encoder LEDs is not needed
2026-02-01 Revert "deleted the RP2040"
    This reverts commit 8df6c2af044ed3c8e394c243da0e06992ad635ca.
2026-02-01 Revert "updated schematic to include encoder and RP2040"
    This reverts commit 9391020f8a8d7e3a289ae9afa1448ef4880317a3.
2026-02-02 added encoder diodes and phototransistors back in
2026-02-02 added power and ground planes to middle layers
    * removed net ties (for now)
    * removed extra gpio pin nets
2026-02-02 assigned pins to encoder phototransistors
    * re-routed some motor driver pins and other stuff
2026-02-03 added BATT and PGND power planes for motor drivers
    started adding traces for phototransistors
2026-02-04 routed IR TOF sensors and IMU
2026-02-04 routed GPIO and debug LEDs
2026-02-05 Updated fillets and profile exports
2026-03-02 Added encoder pattern
2026-03-15 Updated encoder component placement
2026-03-20 Exported encoder blinder
2026-03-20 added placement dxf for encoders to layout
    i think it lines up alright like this
2026-03-20 deleted 11th encoder pin (we only use 10)
2026-03-24 fixing DRC errors.
    routing and placement done.
2026-05-17 WIP version 2
    * (tried to) remove backup files from repo
    * increased current-limiting resistors on green and blue LEDs
    * added pins for motor windings
2026-05-18 added voltage dividers for battery measurement back because I think for now it's still the simplest option
2026-05-18 BOM fully updated, added diodes
    * added another Schottky diode for USB backfeed from 5V line
    * added ESD protection to USB data lines
    * for some reason, LCSC numbers disappeared (i forgot if they were ever
    there), so LCSC numbers added
    * BOM in schematic matches BOM in Notion
2026-05-18 added footprints for motor winding connections
2026-05-19 added nmos driver for encoder LEDs
    and also backup solder jumper in case that doesn't work.
2026-05-19 WIP time to do layout again
    * moved some more stuff to the back of the board
    * need to move more stuff
    * deleted all traces and vias
    * changed standard SMD footprints to hand-solder version
2026-05-21 WIP layout almost done
2026-05-22 everything is connected, DRC passes
    everything in layout is done except for all silkscreen labels
2026-05-23 added pads for shielding
2026-05-26 does not actually pass DRC
    * manufacturing files are added, but that was before I discovered the
    trace spacing issue.
    * trace spacing for inner layers is wrong. minimum spacing is actually
    4mil instead of 3.5mil.
2026-05-29 fixed spacing on middle layer traces
    * updated manufacturing files
    * sent gerbers for fabrication (again)
